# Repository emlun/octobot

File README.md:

octobot
=======

This is a hobby project of building an ALU, CPU, computer, or whatever it ends
up as before I tire of it, from basic components. Think of it as a learning and
art project more than anything practically useful.

Inspirations include:

- [That ALU built in minecraft][minecraft]
- [Boldport Club][boldport-club] for sending me beautiful, fun, whimsical and/or
  useful kits to assemble; and for its community of other tinkerers showing off
  their projects
- [Crash Course Computer Science][cccs] for making me think "that should be fun,
  how hard could it be?"
- The [MOnSter 6502][monster] and [Megaprocessor][megaprocessor]

Special thanks also to the [Boldport Club][boldport-club] community for
providing newbie help as I try to figure these things out!

[cccs]: https://www.youtube.com/watch?v=1I5ZMmrOfnA&list=PL8dPuuaLjXtNlUrzyH5r6jN9ulIgZBpdo&index=6
[minecraft]: https://www.youtube.com/watch?v=LGkkyKZVzug
[boldport-club]: http://www.boldport.club/
[monster]: http://monster6502.com/
[megaprocessor]: https://www.youtube.com/watch?v=z71h9XZbAWY

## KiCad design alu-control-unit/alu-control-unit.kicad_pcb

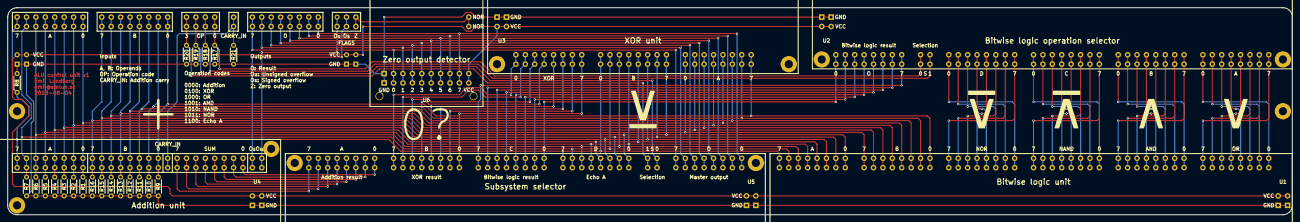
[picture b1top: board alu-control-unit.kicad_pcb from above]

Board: 2 copper layers, 346.7 x 55.9 mm, 35 parts (0 on the bottom side), 90 nets.

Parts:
J1, J2, J5: Conn_01x08; J8x2-double_8_bit_bus_connector_1_indexed
J3: Conn_01x04; J4x2-double_4_bit_bus
J4: Conn_01x01; J1x2-double_1_bit_bus
J6: Conn_01x03; J3x2-double_3_bit_bus
J7, J7#2: PWR-2_pole_power_connector; PWR-double_2_pole_power_connector
R1, R2, R3, R4, R5, R6, R7, R8, R9, R10, R11, R12, R13, R14, R15, R16, R17, R18, R19, R20, R21: R; R_Axial_DIN0204_L3.6mm_D1.6mm_P5.08mm_Horizontal
U1: 8-bit-bitwise-logic
U2, U5: 4-way-8-bit-bus-selector
U3: 8_bit_xor; 8-bit-xor
U4: 8_bit_adder; 8-bit-adder
U6: 8-input-NOR; 8-input-nor

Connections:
/a0: J1.8, R1.2, U1.8, U3.9, U4.8, U5.32
/a1: J1.7, R2.2, U1.7, U3.10, U4.7, U5.31
/a2: J1.6, R3.2, U1.6, U3.11, U4.6, U5.30
/a3: J1.5, R4.2, U1.5, U3.12, U4.5, U5.29
/a4: J1.4, R5.2, U1.4, U3.13, U4.4, U5.28
/a5: J1.3, R6.2, U1.3, U3.14, U4.3, U5.27
/a6: J1.2, R7.2, U1.2, U3.15, U4.2, U5.26
/a7: J1.1, R8.2, U1.1, U3.16, U4.1, U5.25
/and0: U1.40, U2.16
/and1: U1.39, U2.15
/and2: U1.38, U2.14
/and3: U1.37, U2.13
/and4: U1.36, U2.12
/and5: U1.35, U2.11
/and6: U1.34, U2.10
/and7: U1.33, U2.9
/b0: J2.8, R9.2, U1.16, U3.1, U4.16
/b1: J2.7, R10.2, U1.15, U3.2, U4.15
/b2: J2.6, R11.2, U1.14, U3.3, U4.14
/b3: J2.5, R12.2, U1.13, U3.4, U4.13
/b4: J2.4, R13.2, U1.12, U3.5, U4.12
/b5: J2.3, R14.2, U1.11, U3.6, U4.11
/b6: J2.2, R15.2, U1.10, U3.7, U4.10
/b7: J2.1, R16.2, U1.9, U3.8, U4.9
/carry_in: J4.1, R21.2, U4.17
/ins0: J3.4, R17.2, U2.34
/ins1: J3.3, R18.2, U2.33
/ins2: J3.2, R19.2, U5.34
/ins3: J3.1, R20.2, U5.33
/logic_out0: U2.42, U5.24
/logic_out1: U2.41, U5.23
/logic_out2: U2.40, U5.22
/logic_out3: U2.39, U5.21
/logic_out4: U2.38, U5.20
/logic_out5: U2.37, U5.19
/logic_out6: U2.36, U5.18
/logic_out7: U2.35, U5.17
/nand0: U1.32, U2.24
/nand1: U1.31, U2.23
/nand2: U1.30, U2.22
/nand3: U1.29, U2.21
/nand4: U1.28, U2.20
/nand5: U1.27, U2.19
/nand6: U1.26, U2.18
/nand7: U1.25, U2.17
/nor0: U1.24, U2.32
/nor1: U1.23, U2.31
/nor2: U1.22, U2.30
/nor3: U1.21, U2.29
/nor4: U1.20, U2.28
/nor5: U1.19, U2.27
/nor6: U1.18, U2.26
/nor7: U1.17, U2.25
/ofl_sgn: J6.2, U4.26
/ofl_uns: J6.1, U4.27
/or0: U1.48, U2.8
/or1: U1.47, U2.7
/or2: U1.46, U2.6
/or3: U1.45, U2.5
/or4: U1.44, U2.4
/or5: U1.43, U2.3
/or6: U1.42, U2.2
/or7: U1.41, U2.1
/out0: J5.8, U5.42, U6.1
/out1: J5.7, U5.41, U6.2
/out2: J5.6, U5.40, U6.3
/out3: J5.5, U5.39, U6.4
/out4: J5.4, U5.38, U6.5
/out5: J5.3, U5.37, U6.6
/out6: J5.2, U5.36, U6.7
/out7: J5.1, U5.35, U6.8
/out_zero: J6.3, U6.9
/sum0: U4.25, U5.8
/sum1: U4.24, U5.7
/sum2: U4.23, U5.6
/sum3: U4.22, U5.5
/sum4: U4.21, U5.4
/sum5: U4.20, U5.3
/sum6: U4.19, U5.2
/sum7: U4.18, U5.1
/xor0: U3.17, U5.16
/xor1: U3.18, U5.15
/xor2: U3.19, U5.14
/xor3: U3.20, U5.13
/xor4: U3.21, U5.12
/xor5: U3.22, U5.11
/xor6: U3.23, U5.10
/xor7: U3.24, U5.9
GND: J7.1, J7#2.1, R1.1, R2.1, R3.1, R4.1, R5.1, R6.1, R7.1, R8.1, R9.1, R10.1, R11.1, R12.1, R13.1, R14.1, R15.1, R16.1, R17.1, R18.1, R19.1, R20.1, R21.1, U1.50, U2.44, U3.26, U4.29, U5.44, U6.11
VCC: J7.2, J7#2.2, U1.49, U2.43, U3.25, U4.28, U5.43, U6.10

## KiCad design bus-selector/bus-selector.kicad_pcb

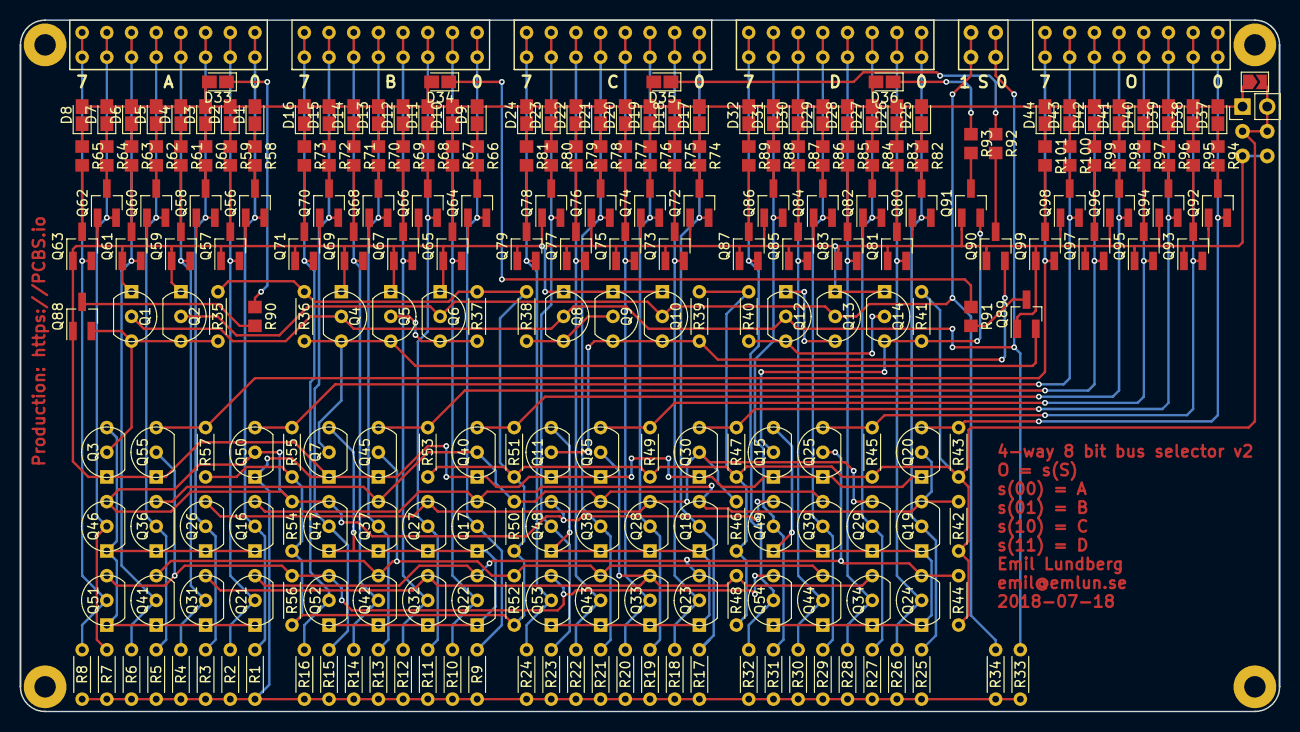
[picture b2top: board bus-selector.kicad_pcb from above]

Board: 2 copper layers, 129.5 x 71.1 mm, 253 parts (0 on the bottom side), 153 nets.

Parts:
D1, D2, D3, D4, D5, D6, D7, D8, D9, D10, D11, D12, D13, D14, D15, D16, D17, D18, D19, D20, D21, D22, D23, D24, D25, D26, D27, D28, D29, D30, D31, D32, D33, D34, D35, D36, D37, D38, D39, D40, D41, D42, D43, D44: LED; LED_0805_2012Metric_Castellated
J1, J2, J3, J4, J6: Conn_01x08; J8x2-double_8_bit_bus_connector_1_indexed
J5: Conn_01x02; J2x2-double_2_bit_bus
J7: PWR-2_pole_power_connector; J2x2-double_2_pole_connector
JP1: Jumper_2_Open; PinHeader_1x02_P2.54mm_Vertical
JP2: SolderJumper_2_Open; SolderJumper-2_P1.3mm_Open_TrianglePad1.0x1.5mm
Q1, Q2, Q3, Q4, Q5, Q6, Q7, Q8, Q9, Q10, Q11, Q12, Q13, Q14, Q15, Q16, Q17, Q18, Q19, Q20, Q21, Q22, Q23, Q24, Q25, Q26, Q27, Q28, Q29, Q30, Q31, Q32, Q33, Q34, Q35, Q36, Q37, Q38, Q39, Q40, Q41, Q42, Q43, Q44, Q45, Q46, Q47, Q48, Q49, Q50, Q51, Q52, Q53, Q54, Q55: 2N7000; TO-92_Molded_Wide_Inline
Q56, Q57, Q58, Q59, Q60, Q61, Q62, Q63, Q64, Q65, Q66, Q67, Q68, Q69, Q70, Q71, Q72, Q73, Q74, Q75, Q76, Q77, Q78, Q79, Q80, Q81, Q82, Q83, Q84, Q85, Q86, Q87, Q88, Q89, Q90, Q91, Q92, Q93, Q94, Q95, Q96, Q97, Q98, Q99: 2N7000; SOT-23_Handsoldering
R1, R2, R3, R4, R5, R6, R7, R8, R9, R10, R11, R12, R13, R14, R15, R16, R17, R18, R19, R20, R21, R22, R23, R24, R25, R26, R27, R28, R29, R30, R31, R32, R33, R34, R35, R36, R37, R38, R39, R40, R41, R42, R43, R44, R45, R46, R47, R48, R49, R50, R51, R52, R53, R54, R55, R56, R57: R; R_Axial_DIN0204_L3.6mm_D1.6mm_P5.08mm_Horizontal
R58, R59, R60, R61, R62, R63, R64, R65, R66, R67, R68, R69, R70, R71, R72, R73, R74, R75, R76, R77, R78, R79, R80, R81, R82, R83, R84, R85, R86, R87, R88, R89, R90, R91, R92, R93, R94, R95, R96, R97, R98, R99, R100, R101: R; R_0805_2012Metric_Pad1.29x1.40mm_HandSolder

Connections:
/LED_PWR: D1.2, D2.2, D3.2, D4.2, D5.2, D6.2, D7.2, D8.2, D9.2, D10.2, D11.2, D12.2, D13.2, D14.2, D15.2, D16.2, D17.2, D18.2, D19.2, D20.2, D21.2, D22.2, D23.2, D24.2, D25.2, D26.2, D27.2, D28.2, D29.2, D30.2, D31.2, D32.2, D33.2, D34.2, D35.2, D36.2, D37.2, D38.2, D39.2, D40.2, D41.2, D42.2, D43.2, D44.2, JP1.1, JP2.1
/a0: J1.1, Q16.2, Q56.2, R1.1
/a1: J1.2, Q21.2, Q57.2, R2.1
/a2: J1.3, Q26.2, Q58.2, R3.1
/a3: J1.4, Q31.2, Q59.2, R4.1
/a4: J1.5, Q36.2, Q60.2, R5.1
/a5: J1.6, Q41.2, Q61.2, R6.1
/a6: J1.7, Q46.2, Q62.2, R7.1
/a7: J1.8, Q51.2, Q63.2, R8.1
/b0: J2.1, Q17.2, Q64.2, R9.1
/b1: J2.2, Q22.2, Q65.2, R10.1
/b2: J2.3, Q27.2, Q66.2, R11.1
/b3: J2.4, Q32.2, Q67.2, R12.1
/b4: J2.5, Q37.2, Q68.2, R13.1
/b5: J2.6, Q42.2, Q69.2, R14.1
/b6: J2.7, Q47.2, Q70.2, R15.1
/b7: J2.8, Q52.2, Q71.2, R16.1
/c0: J3.1, Q18.2, Q72.2, R17.1
/c1: J3.2, Q23.2, Q73.2, R18.1
/c2: J3.3, Q28.2, Q74.2, R19.1
/c3: J3.4, Q33.2, Q75.2, R20.1
/c4: J3.5, Q38.2, Q76.2, R21.1
/c5: J3.6, Q43.2, Q77.2, R22.1
/c6: J3.7, Q48.2, Q78.2, R23.1
/c7: J3.8, Q53.2, Q79.2, R24.1
/d0: J4.1, Q19.2, Q80.2, R25.1
/d1: J4.2, Q24.2, Q81.2, R26.1
/d2: J4.3, Q29.2, Q82.2, R27.1
/d3: J4.4, Q34.2, Q83.2, R28.1
/d4: J4.5, Q39.2, Q84.2, R29.1
/d5: J4.6, Q44.2, Q85.2, R30.1
/d6: J4.7, Q49.2, Q86.2, R31.1
/d7: J4.8, Q54.2, Q87.2, R32.1
/o0: J6.1, Q20.3, Q92.2, R43.2
/o1: J6.2, Q25.3, Q93.2, R45.2
/o2: J6.3, Q30.3, Q94.2, R47.2
/o3: J6.4, Q35.3, Q95.2, R49.2
/o4: J6.5, Q40.3, Q96.2, R51.2
/o5: J6.6, Q45.3, Q97.2, R53.2
/o6: J6.7, Q50.3, Q98.2, R55.2
/o7: J6.8, Q55.3, Q99.2, R57.2
/s0: J5.1, Q1.2, Q4.2, Q8.2, Q12.2, R33.1
/s1: J5.2, Q2.2, Q6.2, Q10.2, Q13.2, R34.1
/sa: Q1.3, Q2.3, Q3.2, Q88.2, R35.2
/sa_and: Q3.3, Q16.1, Q21.1, Q26.1, Q31.1, Q36.1, Q41.1, Q46.1, Q51.1
/sb: Q4.3, Q5.3, Q7.2, Q89.2, R36.2
/sb_and: Q7.3, Q17.1, Q22.1, Q27.1, Q32.1, Q37.1, Q42.1, Q47.1, Q52.1
/sc: Q9.3, Q10.3, Q11.2, Q90.2, R39.2
/sc_and: Q11.3, Q18.1, Q23.1, Q28.1, Q33.1, Q38.1, Q43.1, Q48.1, Q53.1
/sd: Q14.3, Q15.2, Q91.2, R41.2
/sd_and: Q15.3, Q19.1, Q24.1, Q29.1, Q34.1, Q39.1, Q44.1, Q49.1, Q54.1
GND: J7.1, Q1.1, Q2.1, Q3.1, Q4.1, Q5.1, Q6.1, Q7.1, Q8.1, Q9.1, Q10.1, Q11.1, Q13.1, Q14.1, Q15.1, Q20.1, Q25.1, Q30.1, Q35.1, Q40.1, Q45.1, Q50.1, Q55.1, Q56.1, Q57.1, Q58.1, Q59.1, Q60.1, Q61.1, Q62.1, Q63.1, Q64.1, Q65.1, Q66.1, Q67.1, Q68.1, Q69.1, Q70.1, Q71.1, Q72.1, Q73.1, Q74.1, Q75.1, Q76.1, Q77.1, Q78.1, Q79.1, Q80.1, Q81.1, Q82.1, Q83.1, Q84.1, Q85.1, Q86.1, Q87.1, Q88.1, Q89.1, Q90.1, Q91.1, Q92.1, Q93.1, Q94.1, Q95.1, Q96.1, Q97.1, Q98.1, Q99.1, R1.2, R2.2, R3.2, R4.2, R5.2, R6.2, R7.2, R8.2, R9.2, R10.2, R11.2, R12.2, R13.2, R14.2, R15.2, R16.2, R17.2, R18.2, R19.2, R20.2, R21.2, R22.2, R23.2, R24.2, R25.2, R26.2, R27.2, R28.2, R29.2, R30.2, R31.2, R32.2, R33.2, R34.2
unnamed: D1.1, R58.1
unnamed: D2.1, R59.1
unnamed: D3.1, R60.1
unnamed: D4.1, R61.1
unnamed: D5.1, R62.1
unnamed: D6.1, R63.1
unnamed: D7.1, R64.1
unnamed: D8.1, R65.1
unnamed: D9.1, R66.1
unnamed: D10.1, R67.1
unnamed: D11.1, R68.1
unnamed: D12.1, R69.1
unnamed: D13.1, R70.1
unnamed: D14.1, R71.1
unnamed: D15.1, R72.1
unnamed: D16.1, R73.1
unnamed: D17.1, R74.1
unnamed: D18.1, R75.1
unnamed: D19.1, R76.1
unnamed: D20.1, R77.1
unnamed: D21.1, R78.1
unnamed: D22.1, R79.1
unnamed: D23.1, R80.1
unnamed: D24.1, R81.1
unnamed: D25.1, R82.1
unnamed: D26.1, R83.1
unnamed: D27.1, R84.1
unnamed: D28.1, R85.1
unnamed: D29.1, R86.1
unnamed: D30.1, R87.1
unnamed: D31.1, R88.1
unnamed: D32.1, R89.1
unnamed: D33.1, R90.1
unnamed: D34.1, R91.1
unnamed: D35.1, R92.1
unnamed: D36.1, R93.1
unnamed: D37.1, R94.1
unnamed: D38.1, R95.1
unnamed: D39.1, R96.1
unnamed: D40.1, R97.1
unnamed: D41.1, R98.1
unnamed: D42.1, R99.1
unnamed: D43.1, R100.1
unnamed: D44.1, R101.1
unnamed: Q5.2, Q6.3, R37.2
unnamed: Q8.3, Q9.2, R38.2
unnamed: Q12.1, Q13.3
unnamed: Q12.3, Q14.2, R40.2
unnamed: Q16.3, Q17.3, Q18.3, Q19.3, Q20.2, R42.2
unnamed: Q21.3, Q22.3, Q23.3, Q24.3, Q25.2, R44.2
unnamed: Q26.3, Q27.3, Q28.3, Q29.3, Q30.2, R46.2
unnamed: Q31.3, Q32.3, Q33.3, Q34.3, Q35.2, R48.2
unnamed: Q36.3, Q37.3, Q38.3, Q39.3, Q40.2, R50.2
unnamed: Q41.3, Q42.3, Q43.3, Q44.3, Q45.2, R52.2
unnamed: Q46.3, Q47.3, Q48.3, Q49.3, Q50.2, R54.2
unnamed: Q51.3, Q52.3, Q53.3, Q54.3, Q55.2, R56.2
unnamed: Q56.3, R58.2
unnamed: Q57.3, R59.2
unnamed: Q58.3, R60.2
unnamed: Q59.3, R61.2
unnamed: Q60.3, R62.2
unnamed: Q61.3, R63.2
unnamed: Q62.3, R64.2
unnamed: Q63.3, R65.2
unnamed: Q64.3, R66.2
unnamed: Q65.3, R67.2
unnamed: Q66.3, R68.2
unnamed: Q67.3, R69.2
unnamed: Q68.3, R70.2
unnamed: Q69.3, R71.2
unnamed: Q70.3, R72.2
unnamed: Q71.3, R73.2
unnamed: Q72.3, R74.2
unnamed: Q73.3, R75.2
unnamed: Q74.3, R76.2
unnamed: Q75.3, R77.2
unnamed: Q76.3, R78.2
unnamed: Q77.3, R79.2
unnamed: Q78.3, R80.2
unnamed: Q79.3, R81.2
unnamed: Q80.3, R82.2
unnamed: Q81.3, R83.2
unnamed: Q82.3, R84.2
unnamed: Q83.3, R85.2
unnamed: Q84.3, R86.2
unnamed: Q85.3, R87.2
unnamed: Q86.3, R88.2
unnamed: Q87.3, R89.2
unnamed: Q88.3, R90.2
unnamed: Q89.3, R91.2
unnamed: Q90.3, R92.2
unnamed: Q91.3, R93.2
unnamed: Q92.3, R94.2
unnamed: Q93.3, R95.2
unnamed: Q94.3, R96.2
unnamed: Q95.3, R97.2
unnamed: Q96.3, R98.2
unnamed: Q97.3, R99.2
unnamed: Q98.3, R100.2
unnamed: Q99.3, R101.2
VCC: J7.2, JP1.2, JP2.2, R35.1, R36.1, R37.1, R38.1, R39.1, R40.1, R41.1, R42.1, R43.1, R44.1, R45.1, R46.1, R47.1, R48.1, R49.1, R50.1, R51.1, R52.1, R53.1, R54.1, R55.1, R56.1, R57.1

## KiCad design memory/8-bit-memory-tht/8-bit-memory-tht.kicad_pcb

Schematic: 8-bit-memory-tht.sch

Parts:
D1, D2, D3, D4, D5, D6, D7, D8, D9, D10, D11, D12, D13, D14, D15, D16, D17: LED; LED_0805_2012Metric_Pad1.12x1.40mm_HandSolder
J1: J1-1_bit_bus; J1x2-double_1_bit_bus
J2, J3: J8-8_bit_bus_connector; J8x2-double_8_bit_bus_connector
J4: PWR-2_pole_power_connector; J2x2-double_2_pole_connector
JP1: Jumper_2_Open; PinHeader_1x02_P2.54mm_Vertical
JP2: SolderJumper_2_Bridged; SolderJumper-2_P1.3mm_Open_TrianglePad1.0x1.5mm
Q1, Q2, Q3, Q4, Q5, Q6, Q7, Q8, Q9, Q10, Q11, Q12, Q13, Q14, Q15, Q16, Q17, Q18, Q19, Q20, Q21, Q22, Q23, Q24, Q25, Q26, Q27, Q28, Q29, Q30, Q31, Q32, Q33, Q34, Q35, Q36, Q37, Q38, Q39, Q40, Q41, Q42, Q43, Q44, Q45, Q46, Q47, Q48, Q49, Q50, Q51, Q52, Q53, Q54, Q55, Q56, Q57, Q58, Q59, Q60, Q61, Q62, Q63, Q64, Q65, Q66, Q67, Q68, Q69, Q70, Q71, Q72, Q73, Q74, Q75, Q76, Q77, Q78, Q79, Q80, Q81, Q82, Q83, Q84, Q85, Q86, Q87, Q88, Q89: 2N7000; TO-92_Molded_Wide_Inline
Q90, Q91, Q92, Q93, Q94, Q95, Q96, Q97, Q98, Q99, Q100, Q101, Q102, Q103, Q104, Q105, Q106: 2N7000; SOT-23_Handsoldering
R1, R2, R3, R4, R5, R6, R7, R8, R9, R10, R11, R12, R13, R14, R15, R16, R17, R18, R19, R20, R21, R22, R23, R24, R25, R26, R27, R28, R29, R30, R31, R32, R33, R34, R35, R36, R37, R38, R39, R40, R41, R42, R43, R44, R45, R46, R47, R48, R49, R50, R51, R52, R53, R54, R55, R56, R57, R58, R59, R60, R61, R62, R63, R64, R65: R; R_Axial_DIN0204_L3.6mm_D1.6mm_P5.08mm_Horizontal
R66, R67, R68, R69, R70, R71, R72, R73, R74, R75, R76, R77, R78, R79, R80, R81, R82: R; R_0603_1608Metric_Pad0.99x1.00mm_HandSolder

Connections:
/FB0: Q5.2, Q8.3, Q9.3, Q10.2, R6.2
/FB1: Q16.2, Q19.3, Q20.3, Q21.2, R14.2
/FB2: Q27.2, Q30.3, Q31.3, Q32.2, R22.2
/FB3: Q38.2, Q41.3, Q42.3, Q43.2, R30.2
/FB4: Q49.2, Q52.3, Q53.3, Q54.2, R38.2
/FB5: Q60.2, Q63.3, Q64.3, Q65.2, R46.2
/FB6: Q71.2, Q74.3, Q75.3, Q76.2, R54.2
/FB7: Q82.2, Q85.3, Q86.3, Q87.2, R62.2
/I0: J2.0, Q1.2, Q6.2, Q91.2, R1.2
/I1: J2.1, Q12.2, Q17.2, Q92.2, R9.2
/I2: J2.2, Q23.2, Q28.2, Q93.2, R17.2
/I3: J2.3, Q34.2, Q39.2, Q94.2, R25.2
/I4: J2.4, Q45.2, Q50.2, Q95.2, R33.2
/I5: J2.5, Q56.2, Q61.2, Q96.2, R41.2
/I6: J2.6, Q67.2, Q72.2, Q97.2, R49.2
/I7: J2.7, Q78.2, Q83.2, Q98.2, R57.2
/O0: J3.0, Q11.3, Q99.2, R8.2
/O1: J3.1, Q22.3, Q100.2, R16.2
/O2: J3.2, Q33.3, Q101.2, R24.2
/O3: J3.3, Q44.3, Q102.2, R32.2
/O4: J3.4, Q55.3, Q103.2, R40.2
/O5: J3.5, Q66.3, Q104.2, R48.2
/O6: J3.6, Q77.3, Q105.2, R56.2
/O7: J3.7, Q88.3, Q106.2, R64.2
/W: J1.1, Q89.2, Q90.2
/notW: Q3.2, Q7.2, Q14.2, Q18.2, Q25.2, Q29.2, Q36.2, Q40.2, Q47.2, Q51.2, Q58.2, Q62.2, Q69.2, Q73.2, Q80.2, Q84.2, Q89.3, R65.2
GND: J4.1 (GND), Q1.1, Q2.1, Q3.1, Q4.1, Q5.1, Q6.1, Q7.1, Q8.1, Q9.1, Q10.1, Q11.1, Q12.1, Q13.1, Q14.1, Q15.1, Q16.1, Q17.1, Q18.1, Q19.1, Q20.1, Q21.1, Q22.1, Q23.1, Q24.1, Q25.1, Q26.1, Q27.1, Q28.1, Q29.1, Q30.1, Q31.1, Q32.1, Q33.1, Q34.1, Q35.1, Q36.1, Q37.1, Q38.1, Q39.1, Q40.1, Q41.1, Q42.1, Q43.1, Q44.1, Q45.1, Q46.1, Q47.1, Q48.1, Q49.1, Q50.1, Q51.1, Q52.1, Q53.1, Q54.1, Q55.1, Q56.1, Q57.1, Q58.1, Q59.1, Q60.1, Q61.1, Q62.1, Q63.1, Q64.1, Q65.1, Q66.1, Q67.1, Q68.1, Q69.1, Q70.1, Q71.1, Q72.1, Q73.1, Q74.1, Q75.1, Q76.1, Q77.1, Q78.1, Q79.1, Q80.1, Q81.1, Q82.1, Q83.1, Q84.1, Q85.1, Q86.1, Q87.1, Q88.1, Q89.1, Q90.1, Q91.1, Q92.1, Q93.1, Q94.1, Q95.1, Q96.1, Q97.1, Q98.1, Q99.1, Q100.1, Q101.1, Q102.1, Q103.1, Q104.1, Q105.1, Q106.1, R1.1, R9.1, R17.1, R25.1, R33.1, R41.1, R49.1, R57.1
unnamed: D1.1, R66.2
unnamed: D1.2, D2.2, D3.2, D4.2, D5.2, D6.2, D7.2, D8.2, D9.2, D10.2, D11.2, D12.2, D13.2, D14.2, D15.2, D16.2, D17.2, JP1.2, JP2.2
unnamed: D2.1, R67.2
unnamed: D3.1, R68.2
unnamed: D4.1, R69.2
unnamed: D5.1, R70.2
unnamed: D6.1, R71.2
unnamed: D7.1, R72.2
unnamed: D8.1, R73.2
unnamed: D9.1, R74.2
unnamed: D10.1, R75.2
unnamed: D11.1, R76.2
unnamed: D12.1, R77.2
unnamed: D13.1, R78.2
unnamed: D14.1, R79.2
unnamed: D15.1, R80.2
unnamed: D16.1, R81.2
unnamed: D17.1, R82.2
unnamed: Q1.3, Q2.2, R2.2
unnamed: Q2.3, Q3.3, Q4.2, R3.2
unnamed: Q4.3, Q5.3, Q9.2, R4.2
unnamed: Q6.3, Q7.3, Q8.2, R5.2
unnamed: Q10.3, Q11.2, R7.2
unnamed: Q12.3, Q13.2, R10.2
unnamed: Q13.3, Q14.3, Q15.2, R11.2
unnamed: Q15.3, Q16.3, Q20.2, R12.2
unnamed: Q17.3, Q18.3, Q19.2, R13.2
unnamed: Q21.3, Q22.2, R15.2
unnamed: Q23.3, Q24.2, R18.2
unnamed: Q24.3, Q25.3, Q26.2, R19.2
unnamed: Q26.3, Q27.3, Q31.2, R20.2
unnamed: Q28.3, Q29.3, Q30.2, R21.2
unnamed: Q32.3, Q33.2, R23.2
unnamed: Q34.3, Q35.2, R26.2
unnamed: Q35.3, Q36.3, Q37.2, R27.2
unnamed: Q37.3, Q38.3, Q42.2, R28.2
unnamed: Q39.3, Q40.3, Q41.2, R29.2
unnamed: Q43.3, Q44.2, R31.2
unnamed: Q45.3, Q46.2, R34.2
unnamed: Q46.3, Q47.3, Q48.2, R35.2
unnamed: Q48.3, Q49.3, Q53.2, R36.2
unnamed: Q50.3, Q51.3, Q52.2, R37.2
unnamed: Q54.3, Q55.2, R39.2
unnamed: Q56.3, Q57.2, R42.2
unnamed: Q57.3, Q58.3, Q59.2, R43.2
unnamed: Q59.3, Q60.3, Q64.2, R44.2
unnamed: Q61.3, Q62.3, Q63.2, R45.2
unnamed: Q65.3, Q66.2, R47.2
unnamed: Q67.3, Q68.2, R50.2
unnamed: Q68.3, Q69.3, Q70.2, R51.2
unnamed: Q70.3, Q71.3, Q75.2, R52.2
unnamed: Q72.3, Q73.3, Q74.2, R53.2
unnamed: Q76.3, Q77.2, R55.2
unnamed: Q78.3, Q79.2, R58.2
unnamed: Q79.3, Q80.3, Q81.2, R59.2
unnamed: Q81.3, Q82.3, Q86.2, R60.2
unnamed: Q83.3, Q84.3, Q85.2, R61.2
unnamed: Q87.3, Q88.2, R63.2
unnamed: Q90.3, R82.1
unnamed: Q91.3, R66.1
unnamed: Q92.3, R67.1
unnamed: Q93.3, R68.1
unnamed: Q94.3, R69.1
unnamed: Q95.3, R70.1
unnamed: Q96.3, R71.1
unnamed: Q97.3, R72.1
unnamed: Q98.3, R73.1
unnamed: Q99.3, R74.1
unnamed: Q100.3, R75.1
unnamed: Q101.3, R76.1
unnamed: Q102.3, R77.1
unnamed: Q103.3, R78.1
unnamed: Q104.3, R79.1
unnamed: Q105.3, R80.1
unnamed: Q106.3, R81.1
VCC: J4.2 (VCC), JP1.1, JP2.1, R2.1, R3.1, R4.1, R5.1, R6.1, R7.1, R8.1, R10.1, R11.1, R12.1, R13.1, R14.1, R15.1, R16.1, R18.1, R19.1, R20.1, R21.1, R22.1, R23.1, R24.1, R26.1, R27.1, R28.1, R29.1, R30.1, R31.1, R32.1, R34.1, R35.1, R36.1, R37.1, R38.1, R39.1, R40.1, R42.1, R43.1, R44.1, R45.1, R46.1, R47.1, R48.1, R50.1, R51.1, R52.1, R53.1, R54.1, R55.1, R56.1, R58.1, R59.1, R60.1, R61.1, R62.1, R63.1, R64.1, R65.1

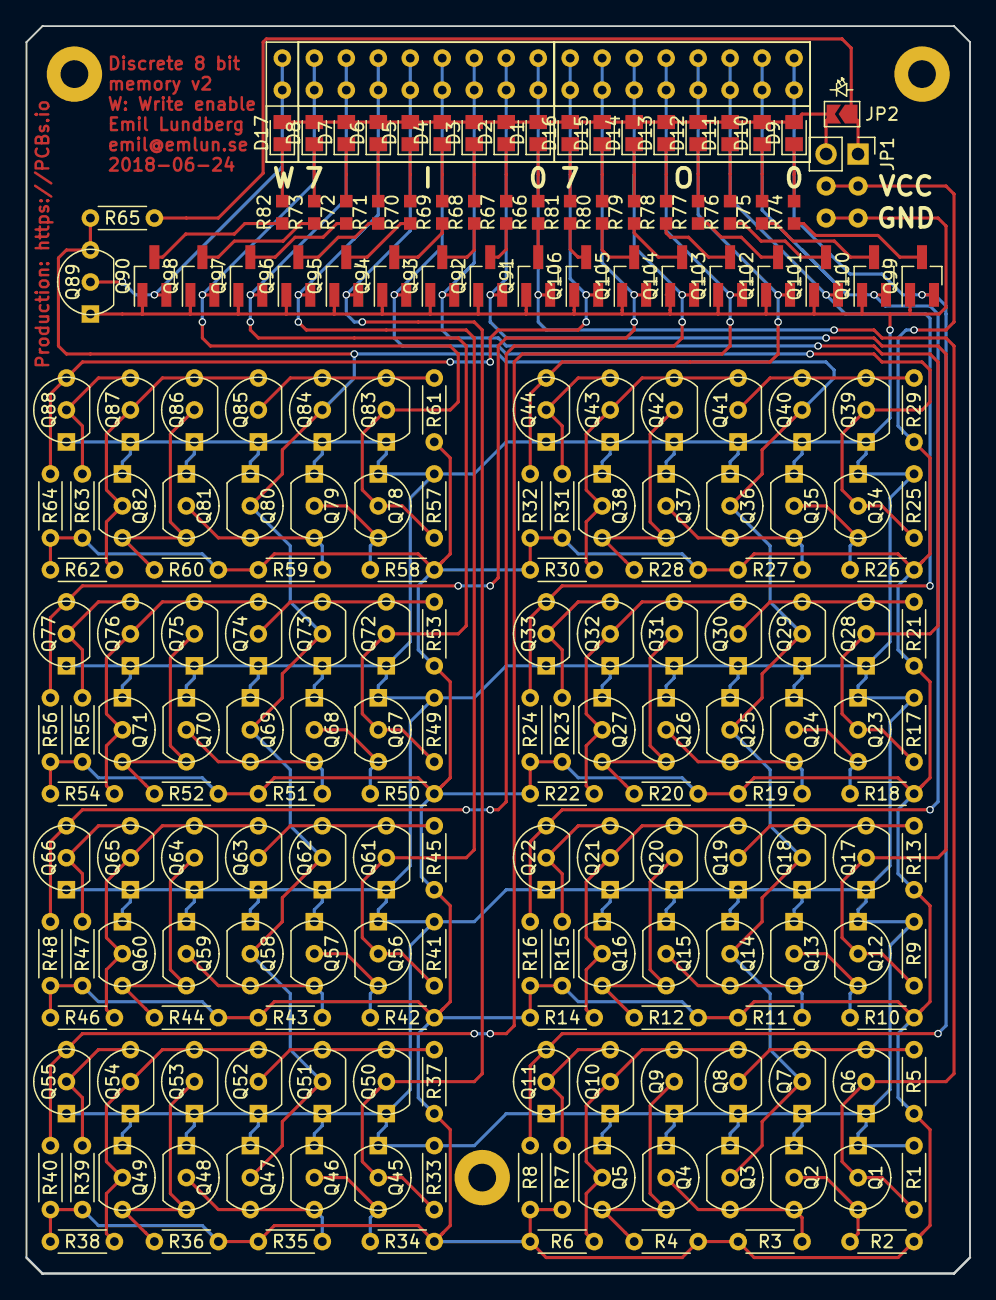
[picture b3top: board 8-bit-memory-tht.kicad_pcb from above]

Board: 2 copper layers, 74.9 x 99.1 mm, 211 parts (0 on the bottom side), 103 nets.

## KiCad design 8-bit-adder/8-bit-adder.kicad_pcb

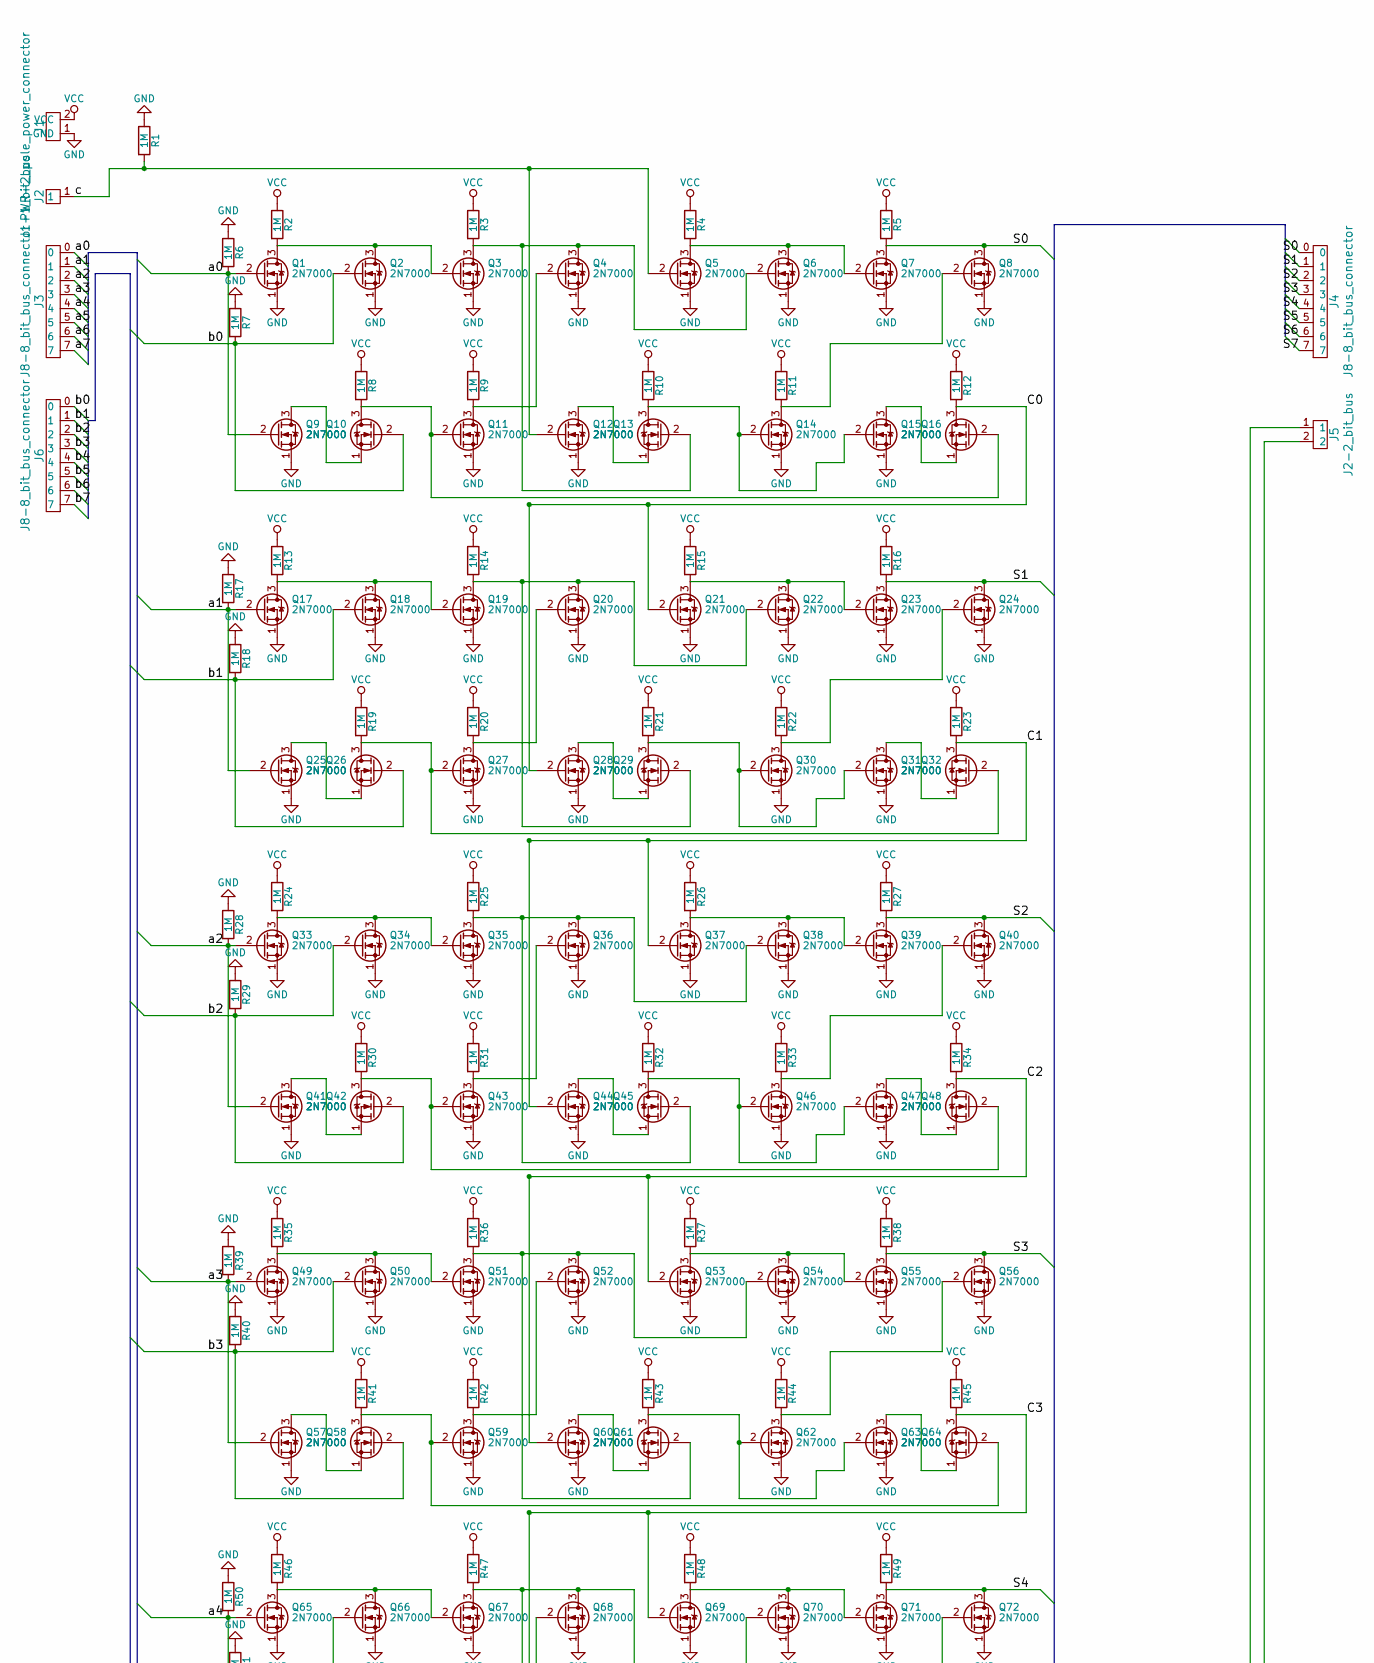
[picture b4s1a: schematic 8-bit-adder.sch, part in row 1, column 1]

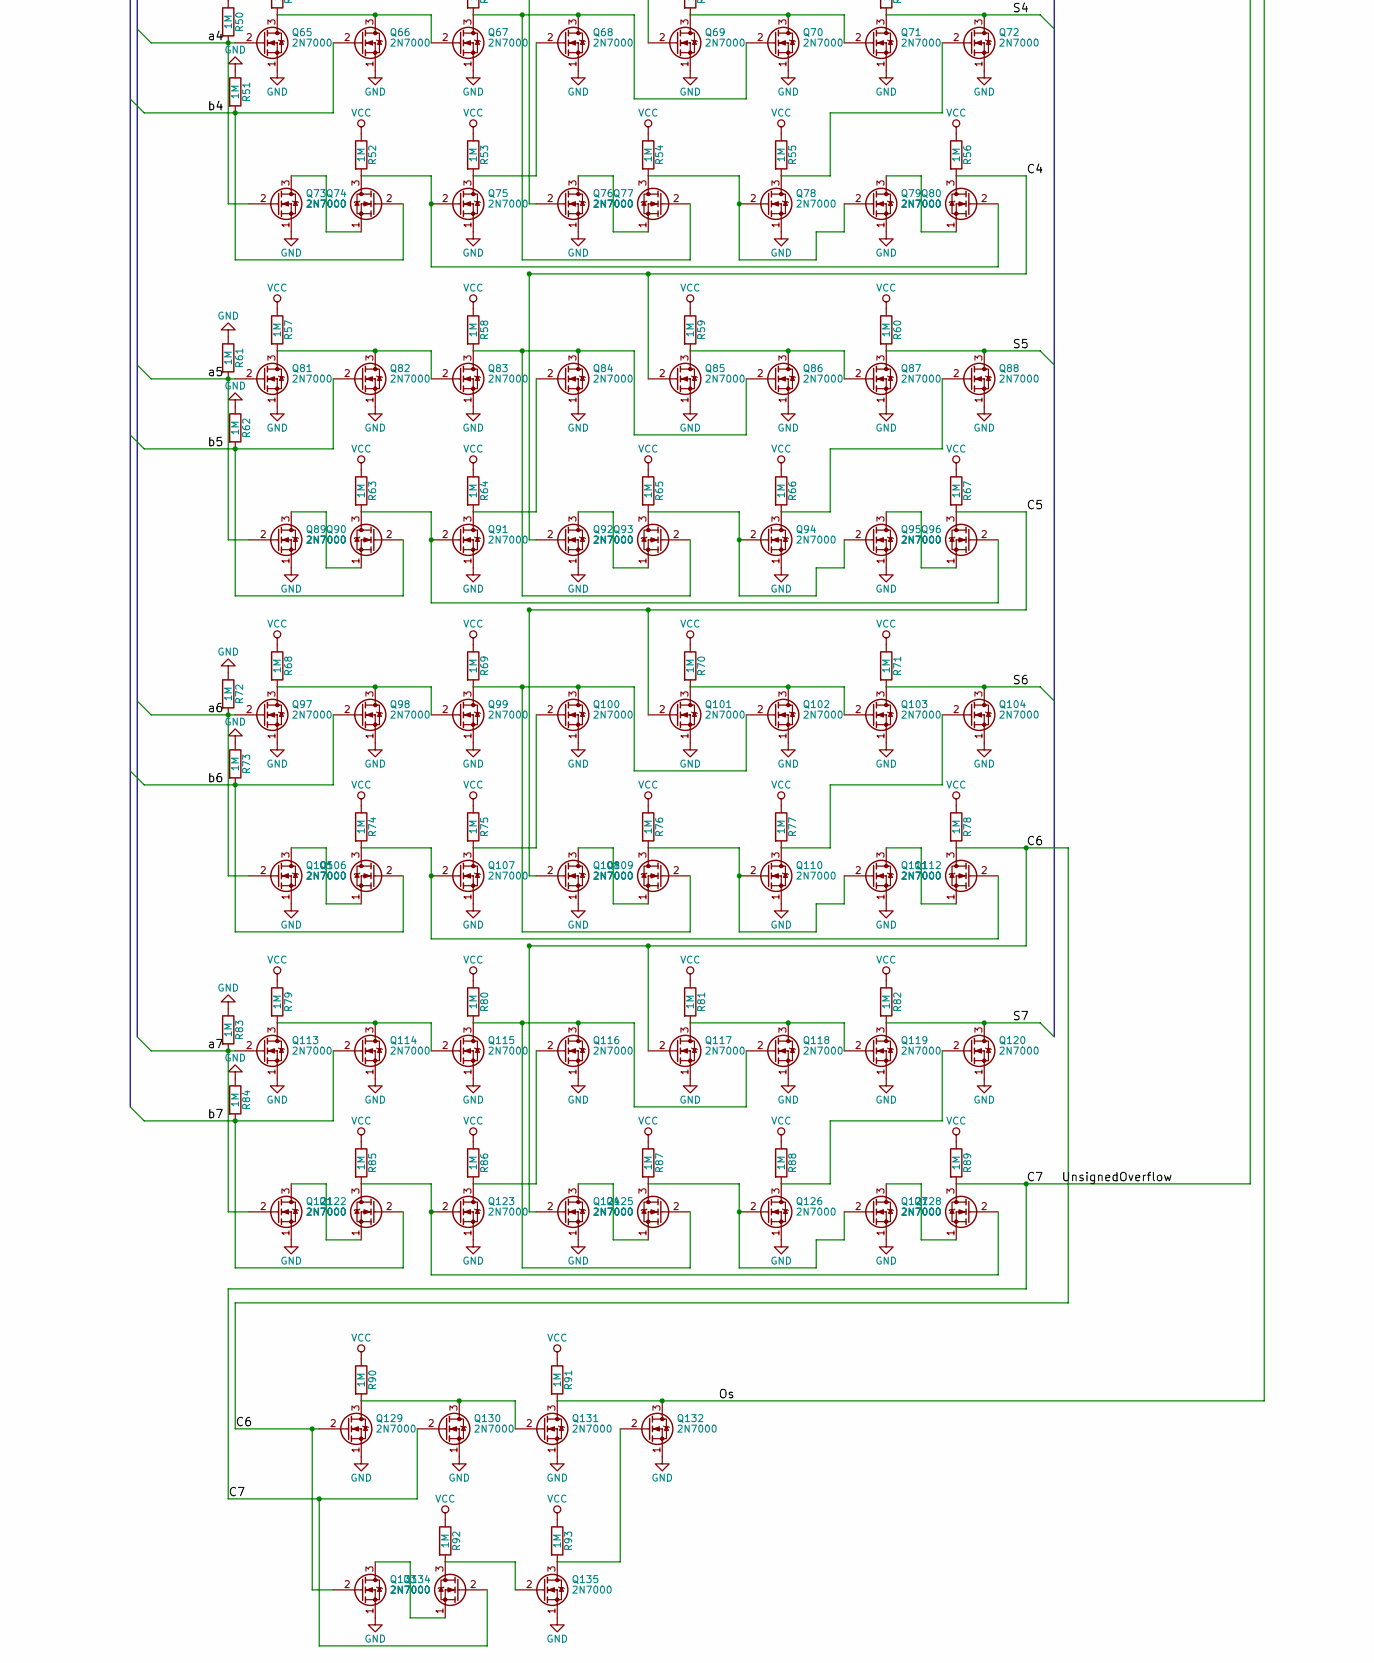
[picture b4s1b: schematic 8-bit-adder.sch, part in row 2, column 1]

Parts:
J1: PWR-2_pole_power_connector; J2x2-double_2_pole_connector
J2: J1-1_bit_bus; J1x2-double_1_bit_bus
J3, J4, J6: J8-8_bit_bus_connector; J8x2-double_8_bit_bus_connector
J5: J2-2_bit_bus; J2x2-double_2_bit_bus
Q1, Q2, Q3, Q4, Q5, Q6, Q7, Q8, Q9, Q10, Q11, Q12, Q13, Q14, Q15, Q16, Q17, Q18, Q19, Q20, Q21, Q22, Q23, Q24, Q25, Q26, Q27, Q28, Q29, Q30, Q31, Q32, Q33, Q34, Q35, Q36, Q37, Q38, Q39, Q40, Q41, Q42, Q43, Q44, Q45, Q46, Q47, Q48, Q49, Q50, Q51, Q52, Q53, Q54, Q55, Q56, Q57, Q58, Q59, Q60, Q61, Q62, Q63, Q64, Q65, Q66, Q67, Q68, Q69, Q70, Q71, Q72, Q73, Q74, Q75, Q76, Q77, Q78, Q79, Q80, Q81, Q82, Q83, Q84, Q85, Q86, Q87, Q88, Q89, Q90, Q91, Q92, Q93, Q94, Q95, Q96, Q97, Q98, Q99, Q100, Q101, Q102, Q103, Q104, Q105, Q106, Q107, Q108, Q109, Q110, Q111, Q112, Q113, Q114, Q115, Q116, Q117, Q118, Q119, Q120, Q121, Q122, Q123, Q124, Q125, Q126, Q127, Q128, Q129, Q130, Q131, Q132, Q133, Q134, Q135: 2N7000; TO-92_Molded_Wide_Inline
R1, R2, R3, R4, R5, R6, R7, R8, R9, R10, R11, R12, R13, R14, R15, R16, R17, R18, R19, R20, R21, R22, R23, R24, R25, R26, R27, R28, R29, R30, R31, R32, R33, R34, R35, R36, R37, R38, R39, R40, R41, R42, R43, R44, R45, R46, R47, R48, R49, R50, R51, R52, R53, R54, R55, R56, R57, R58, R59, R60, R61, R62, R63, R64, R65, R66, R67, R68, R69, R70, R71, R72, R73, R74, R75, R76, R77, R78, R79, R80, R81, R82, R83, R84, R85, R86, R87, R88, R89, R90, R91, R92, R93: 1M; R_Axial_DIN0204_L3.6mm_D1.6mm_P5.08mm_Horizontal

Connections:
/C0: Q16.3 (D), Q21.2 (G), Q28.2 (G), R12.2
/C1: Q32.3 (D), Q37.2 (G), Q44.2 (G), R23.2
/C2: Q48.3 (D), Q53.2 (G), Q60.2 (G), R34.2
/C3: Q64.3 (D), Q69.2 (G), Q76.2 (G), R45.2
/C4: Q80.3 (D), Q85.2 (G), Q92.2 (G), R56.2
/C5: Q96.3 (D), Q101.2 (G), Q108.2 (G), R67.2
/C6: Q112.3 (D), Q117.2 (G), Q124.2 (G), Q129.2 (G), Q133.2 (G), R78.2
/C7: J5.1, Q128.3 (D), Q130.2 (G), Q134.2 (G), R89.2
/Os: J5.2, Q131.3 (D), Q132.3 (D), R91.2
/S0: J4.0, Q7.3 (D), Q8.3 (D), R5.2
/S1: J4.1, Q23.3 (D), Q24.3 (D), R16.2
/S2: J4.2, Q39.3 (D), Q40.3 (D), R27.2
/S3: J4.3, Q55.3 (D), Q56.3 (D), R38.2
/S4: J4.4, Q71.3 (D), Q72.3 (D), R49.2
/S5: J4.5, Q87.3 (D), Q88.3 (D), R60.2
/S6: J4.6, Q103.3 (D), Q104.3 (D), R71.2
/S7: J4.7, Q119.3 (D), Q120.3 (D), R82.2
/a0: J3.0, Q1.2 (G), Q9.2 (G), R6.2
/a1: J3.1, Q17.2 (G), Q25.2 (G), R17.2
/a2: J3.2, Q33.2 (G), Q41.2 (G), R28.2
/a3: J3.3, Q49.2 (G), Q57.2 (G), R39.2
/a4: J3.4, Q65.2 (G), Q73.2 (G), R50.2
/a5: J3.5, Q81.2 (G), Q89.2 (G), R61.2
/a6: J3.6, Q97.2 (G), Q105.2 (G), R72.2
/a7: J3.7, Q113.2 (G), Q121.2 (G), R83.2
/b0: J6.0, Q2.2 (G), Q10.2 (G), R7.2
/b1: J6.1, Q18.2 (G), Q26.2 (G), R18.2
/b2: J6.2, Q34.2 (G), Q42.2 (G), R29.2
/b3: J6.3, Q50.2 (G), Q58.2 (G), R40.2
/b4: J6.4, Q66.2 (G), Q74.2 (G), R51.2
/b5: J6.5, Q82.2 (G), Q90.2 (G), R62.2
/b6: J6.6, Q98.2 (G), Q106.2 (G), R73.2
/b7: J6.7, Q114.2 (G), Q122.2 (G), R84.2
/c: J2.1, Q5.2 (G), Q12.2 (G), R1.2
GND: J1.1 (GND), Q1.1 (S), Q2.1 (S), Q3.1 (S), Q4.1 (S), Q5.1 (S), Q6.1 (S), Q7.1 (S), Q8.1 (S), Q9.1 (S), Q11.1 (S), Q12.1 (S), Q14.1 (S), Q15.1 (S), Q17.1 (S), Q18.1 (S), Q19.1 (S), Q20.1 (S), Q21.1 (S), Q22.1 (S), Q23.1 (S), Q24.1 (S), Q25.1 (S), Q27.1 (S), Q28.1 (S), Q30.1 (S), Q31.1 (S), Q33.1 (S), Q34.1 (S), Q35.1 (S), Q36.1 (S), Q37.1 (S), Q38.1 (S), Q39.1 (S), Q40.1 (S), Q41.1 (S), Q43.1 (S), Q44.1 (S), Q46.1 (S), Q47.1 (S), Q49.1 (S), Q50.1 (S), Q51.1 (S), Q52.1 (S), Q53.1 (S), Q54.1 (S), Q55.1 (S), Q56.1 (S), Q57.1 (S), Q59.1 (S), Q60.1 (S), Q62.1 (S), Q63.1 (S), Q65.1 (S), Q66.1 (S), Q67.1 (S), Q68.1 (S), Q69.1 (S), Q70.1 (S), Q71.1 (S), Q72.1 (S), Q73.1 (S), Q75.1 (S), Q76.1 (S), Q78.1 (S), Q79.1 (S), Q81.1 (S), Q82.1 (S), Q83.1 (S), Q84.1 (S), Q85.1 (S), Q86.1 (S), Q87.1 (S), Q88.1 (S), Q89.1 (S), Q91.1 (S), Q92.1 (S), Q94.1 (S), Q95.1 (S), Q97.1 (S), Q98.1 (S), Q99.1 (S), Q100.1 (S), Q101.1 (S), Q102.1 (S), Q103.1 (S), Q104.1 (S), Q105.1 (S), Q107.1 (S), Q108.1 (S), Q110.1 (S), Q111.1 (S), Q113.1 (S), Q114.1 (S), Q115.1 (S), Q116.1 (S), Q117.1 (S), Q118.1 (S), Q119.1 (S), Q120.1 (S), Q121.1 (S), Q123.1 (S), Q124.1 (S), Q126.1 (S), Q127.1 (S), Q129.1 (S), Q130.1 (S), Q131.1 (S), Q132.1 (S), Q133.1 (S), Q135.1 (S), R1.1, R6.1, R7.1, R17.1, R18.1, R28.1, R29.1, R39.1, R40.1, R50.1, R51.1, R61.1, R62.1, R72.1, R73.1, R83.1, R84.1
unnamed: Q1.3 (D), Q2.3 (D), Q3.2 (G), R2.2
unnamed: Q5.3 (D), Q6.3 (D), Q7.2 (G), R4.2
unnamed: Q9.3 (D), Q10.1 (S)
unnamed: Q10.3 (D), Q11.2 (G), Q16.2 (G), R8.2
unnamed: Q4.2 (G), Q11.3 (D), R9.2
unnamed: Q12.3 (D), Q13.1 (S)
unnamed: Q3.3 (D), Q4.3 (D), Q6.2 (G), Q13.2 (G), R3.2
unnamed: Q13.3 (D), Q14.2 (G), Q15.2 (G), R10.2
unnamed: Q8.2 (G), Q14.3 (D), R11.2
unnamed: Q15.3 (D), Q16.1 (S)
unnamed: Q17.3 (D), Q18.3 (D), Q19.2 (G), R13.2
unnamed: Q19.3 (D), Q20.3 (D), Q22.2 (G), Q29.2 (G), R14.2
unnamed: Q20.2 (G), Q27.3 (D), R20.2
unnamed: Q21.3 (D), Q22.3 (D), Q23.2 (G), R15.2
unnamed: Q24.2 (G), Q30.3 (D), R22.2
unnamed: Q25.3 (D), Q26.1 (S)
unnamed: Q26.3 (D), Q27.2 (G), Q32.2 (G), R19.2
unnamed: Q28.3 (D), Q29.1 (S)
unnamed: Q29.3 (D), Q30.2 (G), Q31.2 (G), R21.2
unnamed: Q31.3 (D), Q32.1 (S)
unnamed: Q33.3 (D), Q34.3 (D), Q35.2 (G), R24.2
unnamed: Q35.3 (D), Q36.3 (D), Q38.2 (G), Q45.2 (G), R25.2
unnamed: Q36.2 (G), Q43.3 (D), R31.2
unnamed: Q37.3 (D), Q38.3 (D), Q39.2 (G), R26.2
unnamed: Q40.2 (G), Q46.3 (D), R33.2
unnamed: Q41.3 (D), Q42.1 (S)
unnamed: Q42.3 (D), Q43.2 (G), Q48.2 (G), R30.2
unnamed: Q44.3 (D), Q45.1 (S)
unnamed: Q45.3 (D), Q46.2 (G), Q47.2 (G), R32.2
unnamed: Q47.3 (D), Q48.1 (S)
unnamed: Q49.3 (D), Q50.3 (D), Q51.2 (G), R35.2
unnamed: Q51.3 (D), Q52.3 (D), Q54.2 (G), Q61.2 (G), R36.2
unnamed: Q52.2 (G), Q59.3 (D), R42.2
unnamed: Q53.3 (D), Q54.3 (D), Q55.2 (G), R37.2
unnamed: Q56.2 (G), Q62.3 (D), R44.2
unnamed: Q57.3 (D), Q58.1 (S)
unnamed: Q58.3 (D), Q59.2 (G), Q64.2 (G), R41.2
unnamed: Q60.3 (D), Q61.1 (S)
unnamed: Q61.3 (D), Q62.2 (G), Q63.2 (G), R43.2
unnamed: Q63.3 (D), Q64.1 (S)
unnamed: Q65.3 (D), Q66.3 (D), Q67.2 (G), R46.2
unnamed: Q67.3 (D), Q68.3 (D), Q70.2 (G), Q77.2 (G), R47.2
unnamed: Q68.2 (G), Q75.3 (D), R53.2
unnamed: Q69.3 (D), Q70.3 (D), Q71.2 (G), R48.2
unnamed: Q72.2 (G), Q78.3 (D), R55.2
unnamed: Q73.3 (D), Q74.1 (S)
unnamed: Q74.3 (D), Q75.2 (G), Q80.2 (G), R52.2
unnamed: Q76.3 (D), Q77.1 (S)
unnamed: Q77.3 (D), Q78.2 (G), Q79.2 (G), R54.2
unnamed: Q79.3 (D), Q80.1 (S)
unnamed: Q81.3 (D), Q82.3 (D), Q83.2 (G), R57.2
unnamed: Q83.3 (D), Q84.3 (D), Q86.2 (G), Q93.2 (G), R58.2
unnamed: Q84.2 (G), Q91.3 (D), R64.2
unnamed: Q85.3 (D), Q86.3 (D), Q87.2 (G), R59.2
unnamed: Q88.2 (G), Q94.3 (D), R66.2
unnamed: Q89.3 (D), Q90.1 (S)
unnamed: Q90.3 (D), Q91.2 (G), Q96.2 (G), R63.2
unnamed: Q92.3 (D), Q93.1 (S)
unnamed: Q93.3 (D), Q94.2 (G), Q95.2 (G), R65.2
unnamed: Q95.3 (D), Q96.1 (S)
unnamed: Q97.3 (D), Q98.3 (D), Q99.2 (G), R68.2
unnamed: Q100.2 (G), Q107.3 (D), R75.2
unnamed: Q99.3 (D), Q100.3 (D), Q102.2 (G), Q109.2 (G), R69.2
unnamed: Q101.3 (D), Q102.3 (D), Q103.2 (G), R70.2
unnamed: Q104.2 (G), Q110.3 (D), R77.2
unnamed: Q105.3 (D), Q106.1 (S)
unnamed: Q106.3 (D), Q107.2 (G), Q112.2 (G), R74.2
unnamed: Q108.3 (D), Q109.1 (S)
unnamed: Q109.3 (D), Q110.2 (G), Q111.2 (G), R76.2
unnamed: Q111.3 (D), Q112.1 (S)
unnamed: Q113.3 (D), Q114.3 (D), Q115.2 (G), R79.2
unnamed: Q115.3 (D), Q116.3 (D), Q118.2 (G), Q125.2 (G), R80.2
unnamed: Q116.2 (G), Q123.3 (D), R86.2
unnamed: Q117.3 (D), Q118.3 (D), Q119.2 (G), R81.2
unnamed: Q120.2 (G), Q126.3 (D), R88.2
unnamed: Q121.3 (D), Q122.1 (S)
unnamed: Q122.3 (D), Q123.2 (G), Q128.2 (G), R85.2
unnamed: Q124.3 (D), Q125.1 (S)
unnamed: Q125.3 (D), Q126.2 (G), Q127.2 (G), R87.2
unnamed: Q127.3 (D), Q128.1 (S)
unnamed: Q129.3 (D), Q130.3 (D), Q131.2 (G), R90.2
unnamed: Q132.2 (G), Q135.3 (D), R93.2
unnamed: Q133.3 (D), Q134.1 (S)
unnamed: Q134.3 (D), Q135.2 (G), R92.2
VCC: J1.2 (VCC), R2.1, R3.1, R4.1, R5.1, R8.1, R9.1, R10.1, R11.1, R12.1, R13.1, R14.1, R15.1, R16.1, R19.1, R20.1, R21.1, R22.1, R23.1, R24.1, R25.1, R26.1, R27.1, R30.1, R31.1, R32.1, R33.1, R34.1, R35.1, R36.1, R37.1, R38.1, R41.1, R42.1, R43.1, R44.1, R45.1, R46.1, R47.1, R48.1, R49.1, R52.1, R53.1, R54.1, R55.1, R56.1, R57.1, R58.1, R59.1, R60.1, R63.1, R64.1, R65.1, R66.1, R67.1, R68.1, R69.1, R70.1, R71.1, R74.1, R75.1, R76.1, R77.1, R78.1, R79.1, R80.1, R81.1, R82.1, R85.1, R86.1, R87.1, R88.1, R89.1, R90.1, R91.1, R92.1, R93.1
